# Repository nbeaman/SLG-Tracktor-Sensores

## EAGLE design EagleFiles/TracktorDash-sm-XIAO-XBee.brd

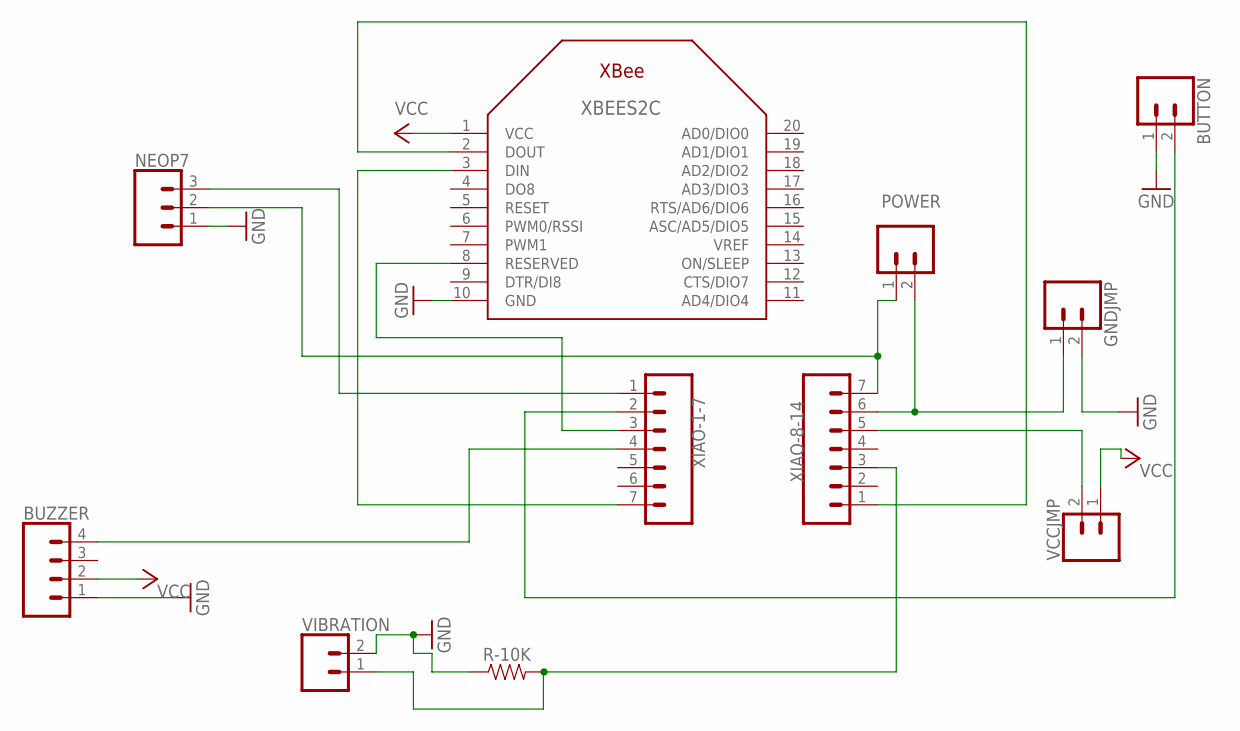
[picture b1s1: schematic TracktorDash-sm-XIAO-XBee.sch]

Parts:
BUTTON: CONN_02; 1X02
BUZZER: CONN_041X04_NO_SILK; 1X04_NO_SILK
GNDJMP: CONN_02; 1X02
NEOP7: 455-1750-1-ND; 1X03
POWER: CONN_02; 1X02
R-10K: 10; AXIAL-0.3
VCCJMP: CONN_02; 1X02
VIBRATION: CONN_02; 1X02
XBEES2C: XBEE
XIAO-1-7, XIAO-8-14: CONN_07; 1X07

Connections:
GND: BUTTON.1, BUZZER.1, GNDJMP.2, NEOP7.1, R-10K.P$1 (1), VIBRATION.2, XBEES2C.10 (GND)
unnamed: NEOP7.3, XIAO-1-7.1
unnamed: VCCJMP.2, XIAO-8-14.5
unnamed: XBEES2C.3 (DIN), XIAO-1-7.7
unnamed: BUTTON.2, XIAO-1-7.2
unnamed: XBEES2C.8 (RESERVED), XIAO-1-7.3
unnamed: BUZZER.4, XIAO-1-7.4
unnamed: NEOP7.2, POWER.1, XIAO-8-14.7
unnamed: XBEES2C.2 (DOUT), XIAO-8-14.1
unnamed: R-10K.P$2 (2), VIBRATION.1, XIAO-8-14.3
unnamed: GNDJMP.1, POWER.2, XIAO-8-14.6
VCC: BUZZER.2, VCCJMP.1, XBEES2C.1 (VCC)

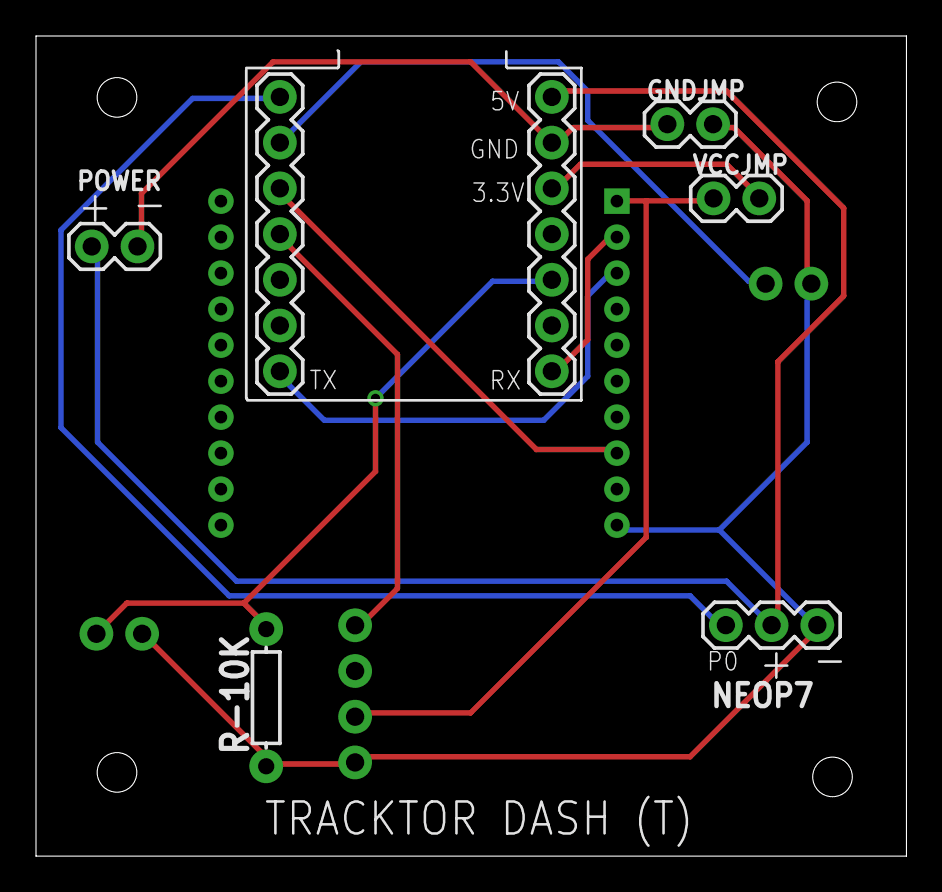
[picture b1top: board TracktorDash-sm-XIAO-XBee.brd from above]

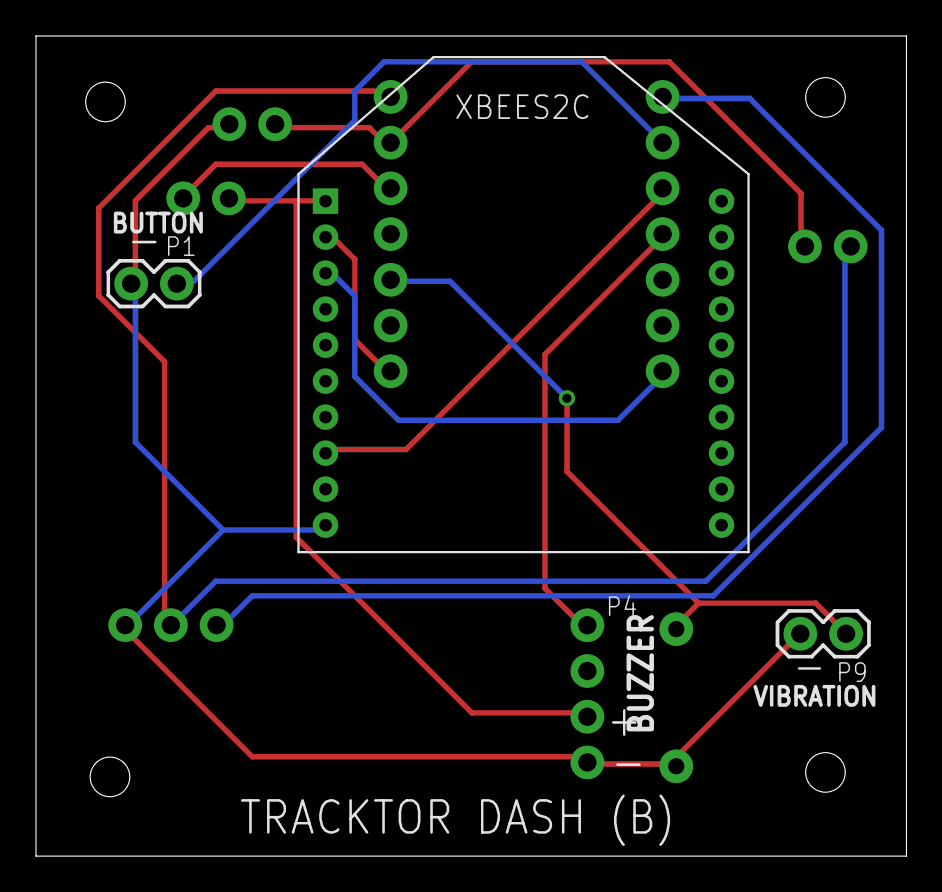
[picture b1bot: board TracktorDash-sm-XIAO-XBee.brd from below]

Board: 2 copper layers, 48.4 x 45.6 mm, 11 parts (4 on the bottom side), 12 nets.

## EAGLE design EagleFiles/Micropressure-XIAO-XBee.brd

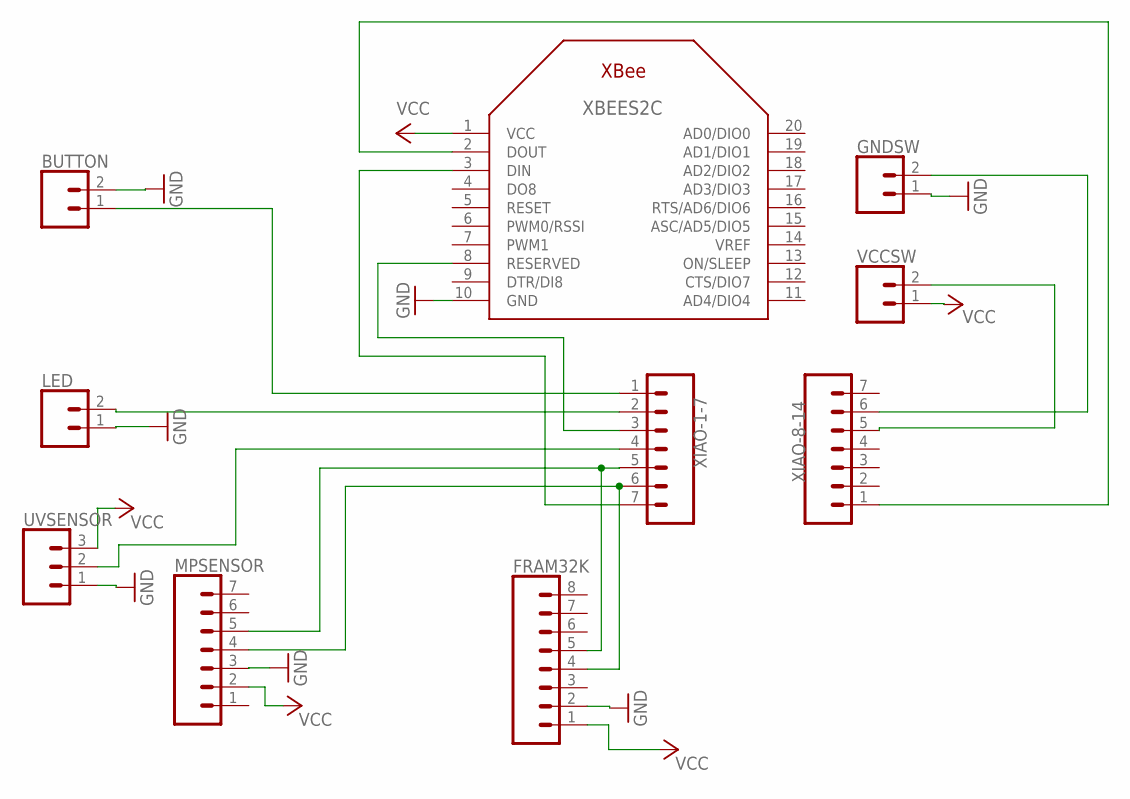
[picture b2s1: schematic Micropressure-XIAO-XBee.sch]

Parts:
BUTTON: button; 1X02
FRAM32K: FRAM32K; 1X08
GNDSW: button; 1X02
LED: LED; 1X02
MPSENSOR: mpsensor; 1X07
UVSENSOR: UV Sensor; 1X03
VCCSW: button; 1X02
XBEES2C: XBEE
XIAO-1-7, XIAO-8-14: CONN_07; 1X07

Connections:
GND: BUTTON.2, FRAM32K.2, GNDSW.1, LED.1, MPSENSOR.3, UVSENSOR.1, XBEES2C.10 (GND)
unnamed: FRAM32K.5, MPSENSOR.5, XIAO-1-7.5
unnamed: FRAM32K.4, MPSENSOR.4, XIAO-1-7.6
unnamed: XBEES2C.3 (DIN), XIAO-1-7.7
unnamed: GNDSW.2, XIAO-8-14.6
unnamed: XBEES2C.8 (RESERVED), XIAO-1-7.3
unnamed: UVSENSOR.2, XIAO-1-7.4
unnamed: BUTTON.1, XIAO-1-7.1
unnamed: LED.2, XIAO-1-7.2
unnamed: XBEES2C.2 (DOUT), XIAO-8-14.1
unnamed: VCCSW.2, XIAO-8-14.5
VCC: FRAM32K.1, MPSENSOR.2, UVSENSOR.3, VCCSW.1, XBEES2C.1 (VCC)

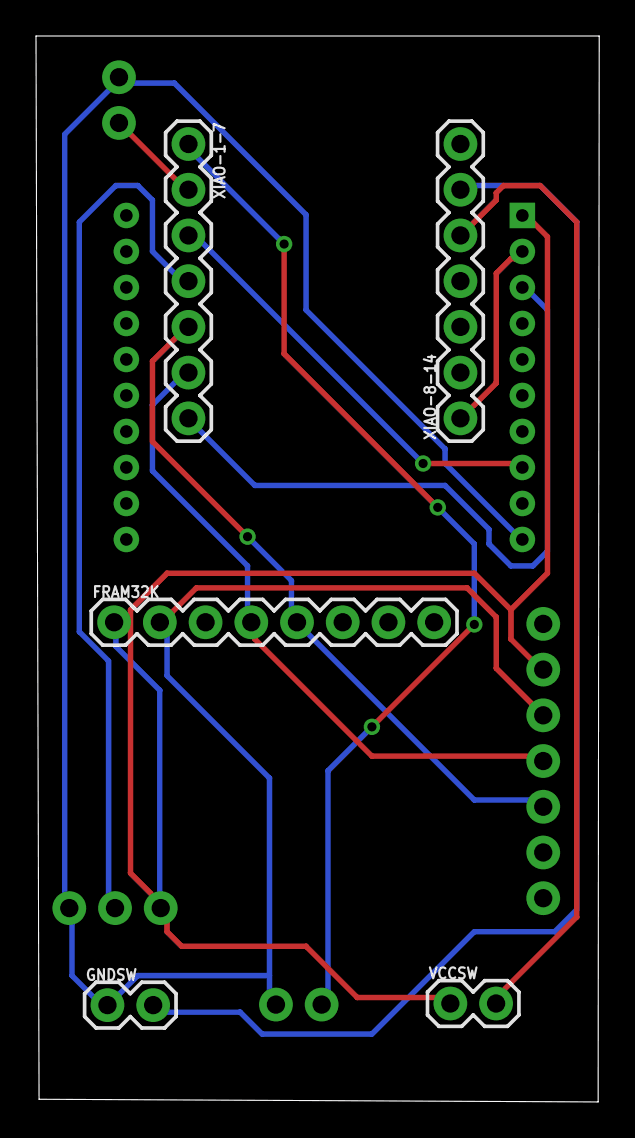
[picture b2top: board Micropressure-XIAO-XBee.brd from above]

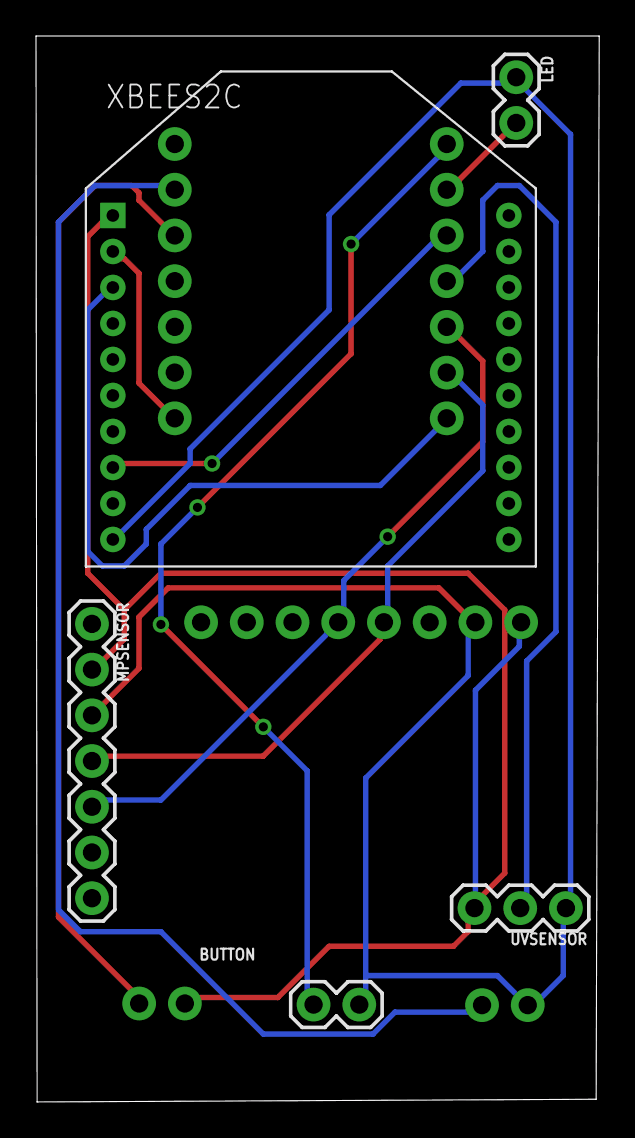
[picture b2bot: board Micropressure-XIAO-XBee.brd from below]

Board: 2 copper layers, 31.3 x 59.2 mm, 10 parts (5 on the bottom side), 12 nets.

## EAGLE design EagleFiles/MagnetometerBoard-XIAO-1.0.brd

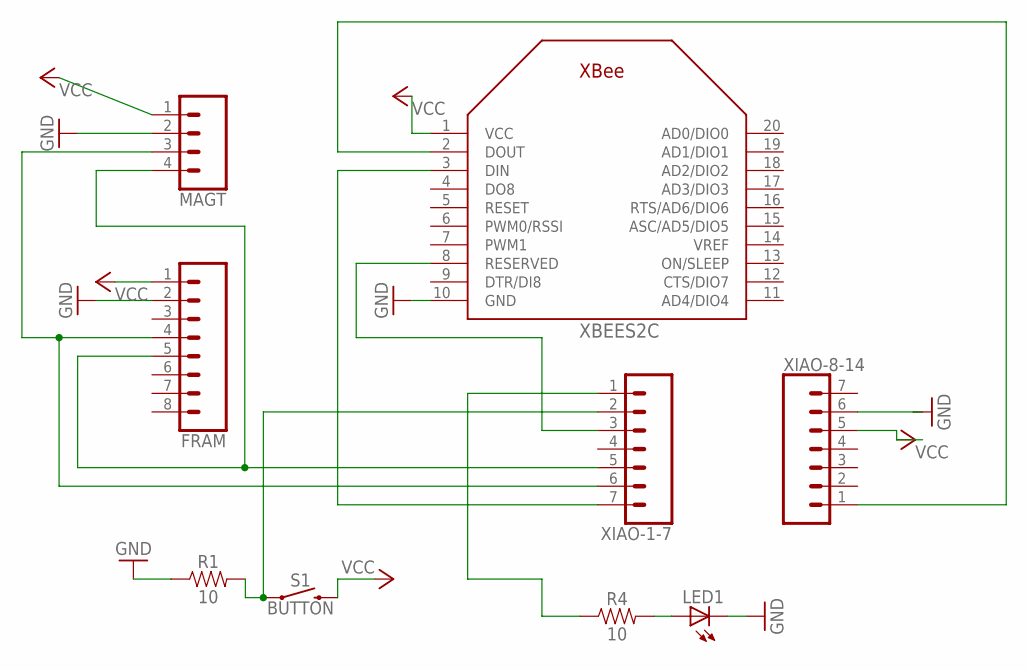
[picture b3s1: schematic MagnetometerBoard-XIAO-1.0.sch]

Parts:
FRAM: CONN_08"; 1X08
LED1: LED3MM
MAGT: CONN_041X04_NO_SILK_NO_POP; 1X04_NO_SILK
R1, R4: 10; AXIAL-0.3
S1: BUTTON; TACTILE_SWITCH_PTH_6.0MM
XBEES2C: XBEE
XIAO-1-7, XIAO-8-14: CONN_07; 1X07

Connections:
GND: FRAM.2, LED1.K (C), MAGT.2, R1.P$1 (1), XBEES2C.10 (GND), XIAO-8-14.6
unnamed: R1.P$2 (2), S1.1, XIAO-1-7.2
unnamed: XBEES2C.3 (DIN), XIAO-1-7.7
unnamed: XBEES2C.8 (RESERVED), XIAO-1-7.3
unnamed: FRAM.4, MAGT.3, XIAO-1-7.6
unnamed: FRAM.5, MAGT.4, XIAO-1-7.5
unnamed: LED1.A, R4.P$2 (2)
unnamed: XBEES2C.2 (DOUT), XIAO-8-14.1
unnamed: R4.P$1 (1), XIAO-1-7.1
VCC: FRAM.1, MAGT.1, S1.3 (2), XBEES2C.1 (VCC), XIAO-8-14.5

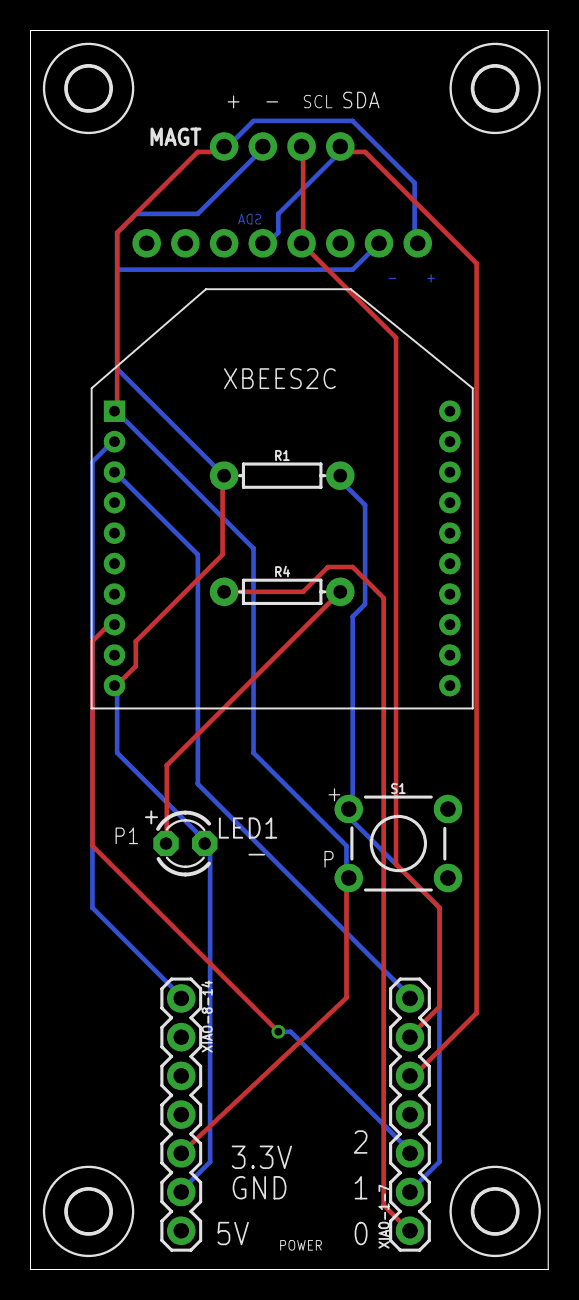
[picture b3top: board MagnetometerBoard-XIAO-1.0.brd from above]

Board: 2 copper layers, 34.0 x 81.3 mm, 13 parts (1 on the bottom side), 10 nets.

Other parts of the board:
U$1, U$2, U$3, U$4: 2,8

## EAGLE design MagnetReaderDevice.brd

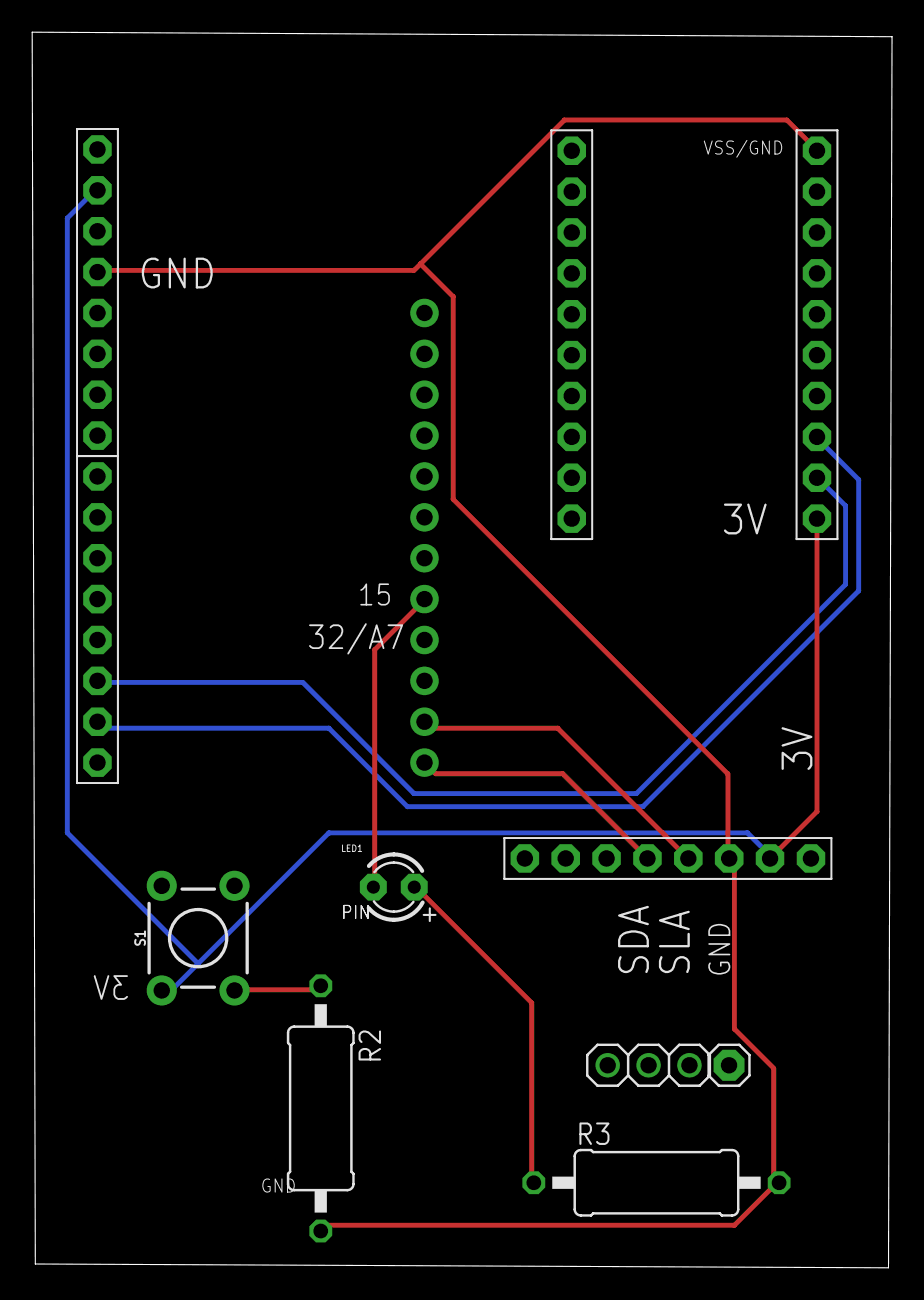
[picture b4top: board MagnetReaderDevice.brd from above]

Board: 2 copper layers, 53.4 x 76.8 mm, 12 parts (0 on the bottom side), 9 nets.

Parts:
JP1: 1X03
JP2, JP6, JP7: 1X08-BIG
JP3: 1X01
JP5: 1X12-CB
LED1: LED3MM
R2, R3: 0411/15
S1: MOMENTARY-SWITCH-SPST-PTH-6.0MM; TACTILE_SWITCH_PTH_6.0MM
U$1, U$2: PINHD-1X10; 1X10-BIG

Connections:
GND: JP2.6, JP6.4, R2.2, R3.2, U$2.10
unnamed: JP2.4, JP5.1
unnamed: R2.1, S1.3
unnamed: JP2.5, JP5.2
unnamed: JP7.6, U$2.2
unnamed: JP5.5, LED1.K
unnamed: LED1.A, R3.1
unnamed: JP7.7, U$2.3
VCC: JP2.7, JP6.2, S1.1, U$2.1

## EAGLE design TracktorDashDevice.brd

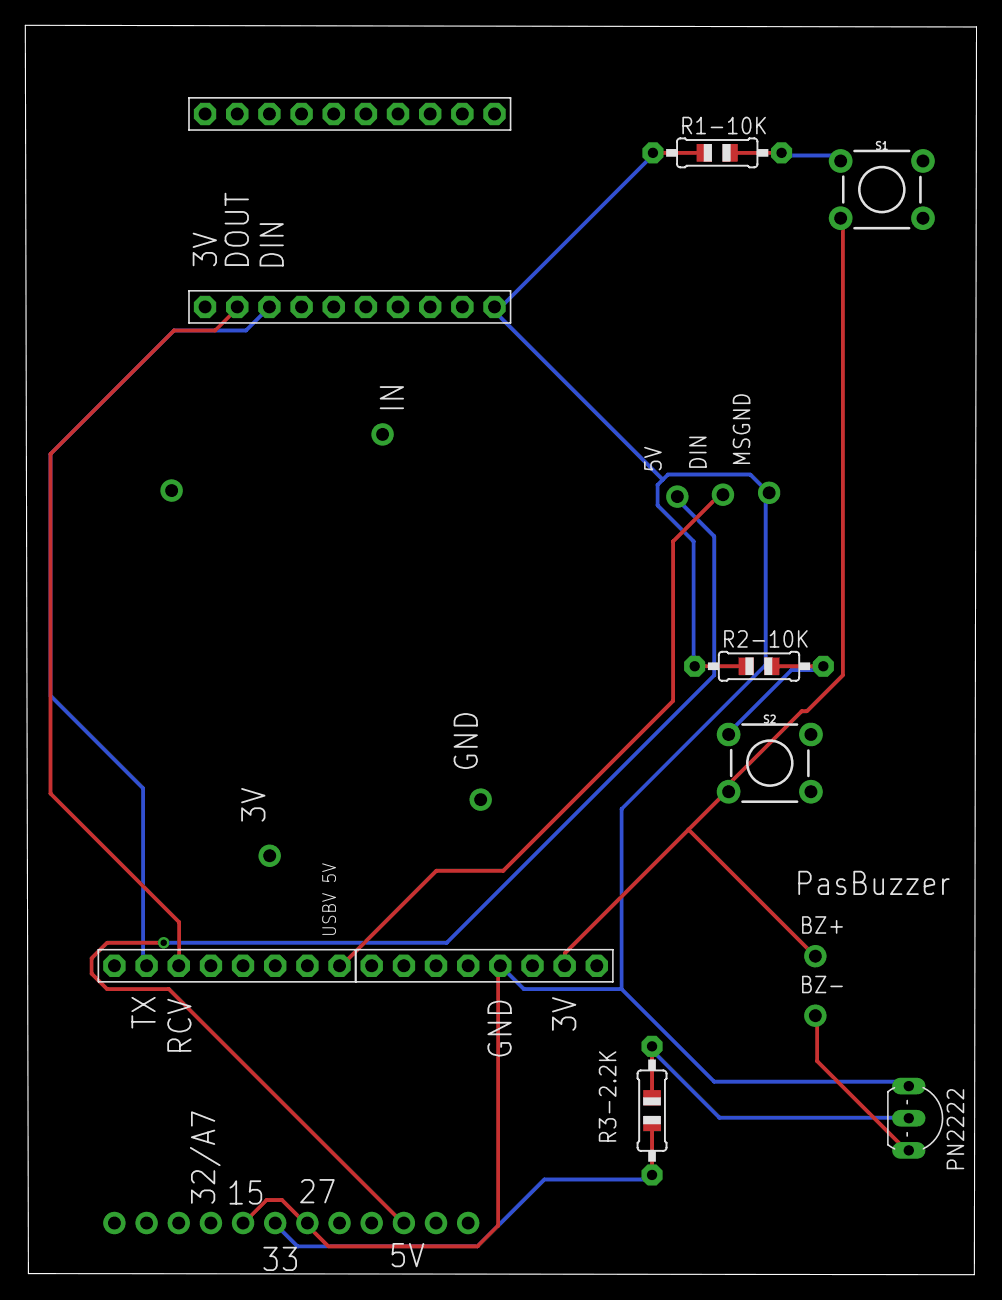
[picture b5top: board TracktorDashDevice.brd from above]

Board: 2 copper layers, 75.1 x 98.7 mm, 20 parts (0 on the bottom side), 12 nets.

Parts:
5V: 1X01-CLEANBIG
BZ+: 1X01-CLEANBIG
BZ-: 1X01-CLEANBIG
DIN: 1X01-CLEANBIG
JP1, JP2, JP3, JP4: 1X01-CLEANBIG
JP5: 1X12-CB
JP6, JP7: 1X08-BIG
MSGND: 1X01-CLEANBIG
PN2222: 2N2907; TO92-EBC-OVAL
R1-10K, R2-10K: 10K; 0805-THM
R3-2.2K: 0805-THM
S1, S2: MOMENTARY-SWITCH-SPST-PTH-6.0MM-KIT; TACTILE_SWITCH_PTH_6.0MM_KIT
U$1, U$2: PINHD-1X10; 1X10-BIG

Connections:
GND: JP4.1, JP5.5, JP5.7, JP6.4, MSGND.1, PN2222.E, R1-10K.1, R2-10K.1, U$2.10
unnamed: DIN.1, JP7.1
unnamed: JP7.7, U$2.3
unnamed: JP2.1, JP5.4
unnamed: JP5.6, R3-2.2K.1
unnamed: JP7.6, U$2.2
unnamed: 5V.1, JP5.10
unnamed: R1-10K.2, S1.1
unnamed: R2-10K.2, S2.1
unnamed: BZ-.1, PN2222.C
unnamed: PN2222.B, R3-2.2K.2
VCC: BZ+.1, JP3.1, JP6.2, S1.3, S2.3, U$2.1

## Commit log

2021-01-03 Initial Code
2021-01-03 Initial EAGLE board file
2021-01-03 Initial EAGLE upload
2021-01-03 Initial EAGLE file upload
2021-01-04 Save normal x y z to EEPROM
2021-01-04 Fixed Buzzer and commented out buttons 1 and 2
2021-01-10 Initial Standard Magnetometer Averages with XIAO
2021-01-12 Initial Upload
2021-01-15 Many Changes
2021-01-17 Initial upload of 32K FRAM Code
2021-01-28 Initial Upload
    Code to test different single devices
2021-01-31 Added Button Code
    one button. when hose connected, press shuts off buzzer. When watering in field, press turns off tank water level status.
2021-02-02 Mute button works better
    change LED 0 in showHoseConnectedAlertLEDs() this function was called colorSwipe() previously.
2021-02-02 New Code for Magnet Reader
    better xbee communication.
2021-02-10 Much cleaner/faster XBee readings
    Before water tank data introduced to code
2021-02-10 Faster read of values
    slow or no delay
2021-02-10 after cable splice to allow programming
2021-02-11 hoseConnectValueOnly for when payload is mixed
2021-02-12 Tank Level LEDS Working
2021-02-15 Change delay to 4 seconds
2021-02-15 changed delay to 4 seconds
2021-02-15 Test what an xbee is Reading
2021-02-16 Show ? if no data in 20 seconds
2021-03-13 Initial upload
    FRAM is situated correctly and button (normally HIGH) changed from VCC to GRN to correct mistake
2021-03-14 2ND ORDER PCBWAY
    FRAM ORIANTATION AND CONNECTIONS FIXED
2021-03-14 2ND PCBWay Order

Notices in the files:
parts and their libraries:
SparkFun-Connectors: Licensing: Creative Commons ShareAlike 4.0 International - https://creativecommons.org/licenses/by-sa/4.0
